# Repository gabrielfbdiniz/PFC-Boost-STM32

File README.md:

# AC-DC 380V Active Boost PFC Converter

-red.svg)

-purple.svg)

Conversor estático de potência CA/CC com **Correção Ativa do Fator de Potência (Active PFC)** na topologia **Boost**, projetado para elevar a tensão da rede elétrica retificada (127V / 220V AC) para um barramento CC estabilizado de **380V DC**.

O controle digital de malha fechada (tensão e corrente em modo de condução contínua - CCM) e gerenciamento de estados é operado por uma plataforma **STM32F103C8T6 (ARM Cortex-M3 a 72 MHz)**, acompanhado de proteções ultrarrápidas de sobrecorrente por hardware e circuito inteligente de pré-carga (*soft-start / inrush current limiting*).

---

## Renderizações 3D do Projeto

| Vista Superior (Top View) | Vista Inferior (Bottom View) |
| :---: | :---: |
|  |  |

| Perspectiva Superior Isométrica | Perspectiva Inferior Isométrica |
| :---: | :---: |
|  |  |

---

## 1. Visão Geral da Arquitetura do Conversor

O sistema é dividido em três blocos funcionais modulares conforme o esquemático hierárquico:
1. **Low Frequency Rectifier & Inrush (`lf_rectifier`):** Ponte retificadora de entrada, relé de bypass de inrush (`RELAY_INRUSH`) e relé mestre de ligamento (`RELAY_ON_OFF`).
2. **Estágio de Potência & Proteção PFC (`pfc`):** Indutor boost, MOSFET de comutação rápida, diodo boost ultrarrápido, gate driver com porta de intertravamento e latch analógico de sobrecorrente em hardware.
3. **Placa de Controle & IHM (`mcu`):** Breakout STM32F103 (Blue Pill), conversores de nível lógico, display I2C, encoder rotativo e acionamento térmico do ventilador.

```mermaid
flowchart LR
    subgraph AC_Input["Entrada de Rede"]
        AC["Rede CA (127V / 220V)"] --> INRUSH["Circuito de Pré-carga & Inrush"]
        INRUSH --> BRIDGE["Ponte Retificadora"]
    end

    subgraph PFC_Stage["Estágio Boost PFC (Alta Tensão)"]
        BRIDGE -->|"V_in retificada"| L["Indutor Boost L1"]
        L --> Q["MOSFET Q3"]
        L --> D["Diodo Boost D15"]
        D --> COUT["Banco Capacitivo (380V DC)"]
        Q --> SHUNT["Sensor de Corrente"]
    end

    subgraph Hardware_Protection["Proteção Hardware OCP"]
        SHUNT --> COMP["Comparador Rápido (LMV7219)"]
        COMP --> LATCH["Latch SR (74HC00)"]
        LATCH -->|"Hard-Trip Inibição"| AND_GATE["Porta AND (74LVC1G08)"]
        AND_GATE --> DRIVER["Gate Driver TC4427"]
        DRIVER --> Q
    end

    subgraph MCU_Control["Controle Digital (STM32 Blue Pill)"]
        COUT -.->|"Sensoriamento Vout (ADC)"| MCU["STM32F103C8T6"]
        BRIDGE -.->|"Sensoriamento Vin (ADC)"| MCU
        SHUNT -.->|"Sensoriamento IL (ADC)"| MCU
        MCU -->|"PWM Alta Frequência"| AND_GATE
        MCU -->|"RESET_OC"| LATCH
        MCU -->|"ENABLE Geral"| AND_GATE
        MCU -->|"Comando Relés"| INRUSH
    end
```

---

## 2. Especificações Técnicas

| Parâmetro | Valor / Faixa | Observações |
| :--- | :--- | :--- |
| **Topologia** | Boost PFC Ativo (CCM) | Fator de Potência $> 0.98$ |
| **Tensão de Entrada ($V_{in}$)** | $127\text{ V}_{\text{RMS}} - 220\text{ V}_{\text{RMS}}$ ($60\text{ Hz}$) | Tensão de pico retificada: $\approx 180\text{ V} - 311\text{ V}$ |
| **Tensão de Saída ($V_{out}$)** | **$380\text{ V DC}$ regulada** | Tensão nominal do barramento CC |
| **Controlador** | STM32F103C8T6 (ARM Cortex-M3) | 72 MHz, 64 KB Flash, ADC 12 bits |
| **Chaveamento Principal** | MOSFET TO-220 + Diodo Boost TO-220 | Dissipadores dimensionados para convecção forçada |
| **Driver de Gate** | Microchip TC4427 + Intertravamento 74LVC1G08 | Resposta sub-microssegundo |
| **Proteção de Sobrecorrente (OCP)** | Comparador LMV7219 + Latch 74HC00 | Desligamento por hardware independente do MCU |
| **Pré-carga de Barramento** | Relés de 2 estágios (`INRUSH` e `ON_OFF`) | Protege diodos e banco capacitivo na energização |
| **Interface do Usuário** | Display I2C + Encoder Rotativo com Push-Button | Navegação de menus, leituras e parametrização |
| **Refrigeração** | Saída controlada de 12V para Ventoinha | Acionamento via transistor comutada por PWM/GPIO |

---

## 3. Pinout & Mapeamento do Microcontrolador (STM32 Blue Pill)

O mapeamento de pinos reflete as conexões reais implementadas nas folhas esquemáticas em [`hardware/`](hardware/) e roteadas na placa de circuito impresso:

### Pinos de Potência, Controle e Atuadores

| Pino Blue Pill | Sinal Associado | Função no Hardware | Descrição / Operação |
| :--- | :--- | :--- | :--- |
| **`PA2`** | `PFC_PWM` | `TIM2_CH3` | Sinal PWM de alta frequência (50 a 100 kHz) para comutação do MOSFET via gate driver |
| **`PB10`** | `RELAY_INRUSH`| GPIO Output | Aciona o relé de limitação de corrente de partida (bypass do termistor NTC) |
| **`PB11`** | `RELAY_ON_OFF`| GPIO Output | Aciona o relé principal de energização da rede CA |
| **`PB12`** | `FAN_CTRL` | GPIO Output | Controle liga/desliga da ventoinha de refrigeração forçada |
| **`PB8`** | `I2C1_SCL` | `I2C1` | Clock do barramento serial I2C (Display OLED 0.96" SSD1306) com pull-up de 4.7kΩ |
| **`PB9`** | `I2C1_SDA` | `I2C1` | Dados do barramento serial I2C (Display OLED 0.96" SSD1306) com pull-up de 4.7kΩ |
| **`PB3`** | `EXP_SCK` | `SPI1_SCK` / GPIO | Barramento de expansão frontal / Interface de usuário (`J2`) |
| **`PB4`** | `EXP_MISO` | `SPI1_MISO` / GPIO | Barramento de expansão frontal / Interface de usuário (`J2`) |
| **`PB5`** | `EXP_MOSI` | `SPI1_MOSI` / GPIO | Barramento de expansão frontal / Interface de usuário (`J2`) |
| **`PA15`** | `EXP_CS` | GPIO Output | Chip-select para periféricos de expansão no conector `J2` |

### Sensoriamento Analógico e Medição

| Pino Blue Pill | Sinal Associado | Função no Hardware | Descrição / Operação |
| :--- | :--- | :--- | :--- |
| **`PA7`** | `PFC_IL` | `ADC1_IN7` | Sensoriamento analógico da corrente no indutor boost (amplificador de shunt) |
| **`PB0`** | `PFC_VOUT`| `ADC1_IN8` | Sensoriamento da tensão de saída do barramento CC estabilizado (380V) |
| **`PB1`** | `PFC_VIN` | `ADC1_IN9` | Sensoriamento da tensão senoidal retificada de entrada |
| **`PC13`** | *LED Onboard* | GPIO Output | LED indicador de batimento cardíaco (*heartbeat*) e status operacional |
| **`PA13`/`PA14`** | `SWD` | `SWDIO` / `SWCLK` | Interface de gravação e depuração em tempo real com ST-Link v2 |

## 4. Circuitos de Proteção e Segurança em Hardware

1. **Proteção Ultrarrápida de Sobrecorrente (Hardware Trip):**
   * Em conversores boost, sobrecorrentes na chave podem queimar semicondutores em microssegundos.
   * O sinal do resistor shunt de corrente é monitorado continuamente pelo comparador analógico **LMV7219** (`U2`).
   * A saída do comparador aciona imediatamente um **Latch SR implementado com portas NAND 74HC00** (`U5`), travando a saída em nível lógico baixo e cortando a porta AND `74LVC1G08` (`U6`) antes mesmo do firmware do MCU tomar conhecimento.
   * O destravamento após mitigação só ocorre mediante pulso explícito do pino `RESET_OC`.

2. **Sequenciamento de Energização e Pré-Carga:**
   * Na energização inicial, o relé `RELAY_INRUSH` comuta o fluxo de corrente por resistores limitadores de alta potência até os capacitores de saída carregarem sem picos destrutivos.
   * Ao atingir o patamar nominal de entrada, o relé mestre `RELAY_ON_OFF` fecha o circuito em paralelo e o conversor pode ser habilitado com segurança.

---

## 5. Estrutura do Repositório

```text
├── hardware/                   # Projeto de Hardware no KiCad 10
│   ├── 3d/                     # Modelos CAD 3D dos componentes (STEP / WRL)
│   │   ├── Capacitor_THT_L28.0mm_W11.0mm_P25.00mm.step # Modelo 3D dos capacitores C11 e C12
│   │   ├── Inductor_NEE-30-15-15.step                  # Modelo 3D do indutor boost L1 (NEE-30)
│   │   └── ...                 # Modelos adicionais (STM32 Blue Pill, bornes, conectores)
│   ├── lf_rectifier.kicad_sch  # Sub-folha: Retificação de baixa frequência e inrush
│   ├── mcu.kicad_sch           # Sub-folha: Módulo MCU Blue Pill e conexões de IHM
│   ├── pfc.kicad_sch           # Sub-folha: Estágio Boost PFC de 380V e circuitos de proteção
│   ├── power-supply.kicad_pcb  # Layout e roteamento completo da PCB
│   ├── power-supply.kicad_pro  # Arquivo de gerenciamento do projeto KiCad 10
│   └── power-supply.kicad_sch  # Esquemático principal (Top-Level Sheet)
├── firmware/                   # Firmware embarcado para STM32F103 (STM32CubeIDE 1.19)
│   └── README.md               # Guia de configuração, pinout, FSM e arquitetura
├── simulation/                 # Simulação computacional e controle
│   └── simulate_pfc_control.py # Comparação de malhas de controle (Cascata Energia vs. Jacobiano)
├── docs/                       # Documentação técnica e esquemáticos vetoriais
│   ├── PFC_380V_Schematic.pdf  # Esquemático completo exportado em PDF vetorial
│   └── pfc_control_comparison.png # Gráficos comparativos de controle
├── renders/                    # Renders 3D fotorrealistas em alta resolução (1080p)
│   ├── render_top.png
│   ├── render_bottom.png
│   ├── render_iso_top.png
│   └── render_iso_bottom.png
├── .gitignore                  # Filtro para temporários, builds e caches
├── LICENSE                     # Licença de Hardware Aberto CERN-OHL-S v2
└── README.md                   # Documentação técnica de engenharia
```

---

## 6. Como Abrir e Validar o Projeto

### Pré-requisitos
* **KiCad EDA 10.0+** instalado no sistema.
* **Python 3.10+** (com `numpy` e `matplotlib`) para as simulações numéricas.
* **STM32CubeIDE 1.19** para o desenvolvimento do firmware.

### Regenerar Renderizações 3D (via Linha de Comando)
```bash
kicad-cli pcb render -o renders/render_top.png --width 1920 --height 1080 --side top --quality high hardware/power-supply.kicad_pcb
kicad-cli pcb render -o renders/render_bottom.png --width 1920 --height 1080 --side bottom --quality high hardware/power-supply.kicad_pcb
kicad-cli pcb render -o renders/render_iso_top.png --width 1920 --height 1080 --rotate -45,0,45 --quality high hardware/power-supply.kicad_pcb
kicad-cli pcb render -o renders/render_iso_bottom.png --width 1920 --height 1080 --side bottom --rotate -45,0,45 --quality high hardware/power-supply.kicad_pcb
```

### Exportar Esquemático em PDF
```bash
kicad-cli sch export pdf -o docs/PFC_380V_Schematic.pdf hardware/power-supply.kicad_sch
```

### Executar a Simulação Comparativa de Controle
```bash
python simulation/simulate_pfc_control.py
```

## 7. Licença & Créditos

### Autores & Desenvolvedores
* **Abílio Davi**
* **Gabriel Diniz**
* **Vinicius Moreira**

### Orientação
* **Professor Colombo**
* **Professor Eduardo Lenz**

---

### Licença
Distribuído sob a licença **CERN-OHL-S v2** (*CERN Open Hardware Licence Strongly Reciprocal*). Consulte o arquivo [LICENSE](LICENSE) para mais detalhes.

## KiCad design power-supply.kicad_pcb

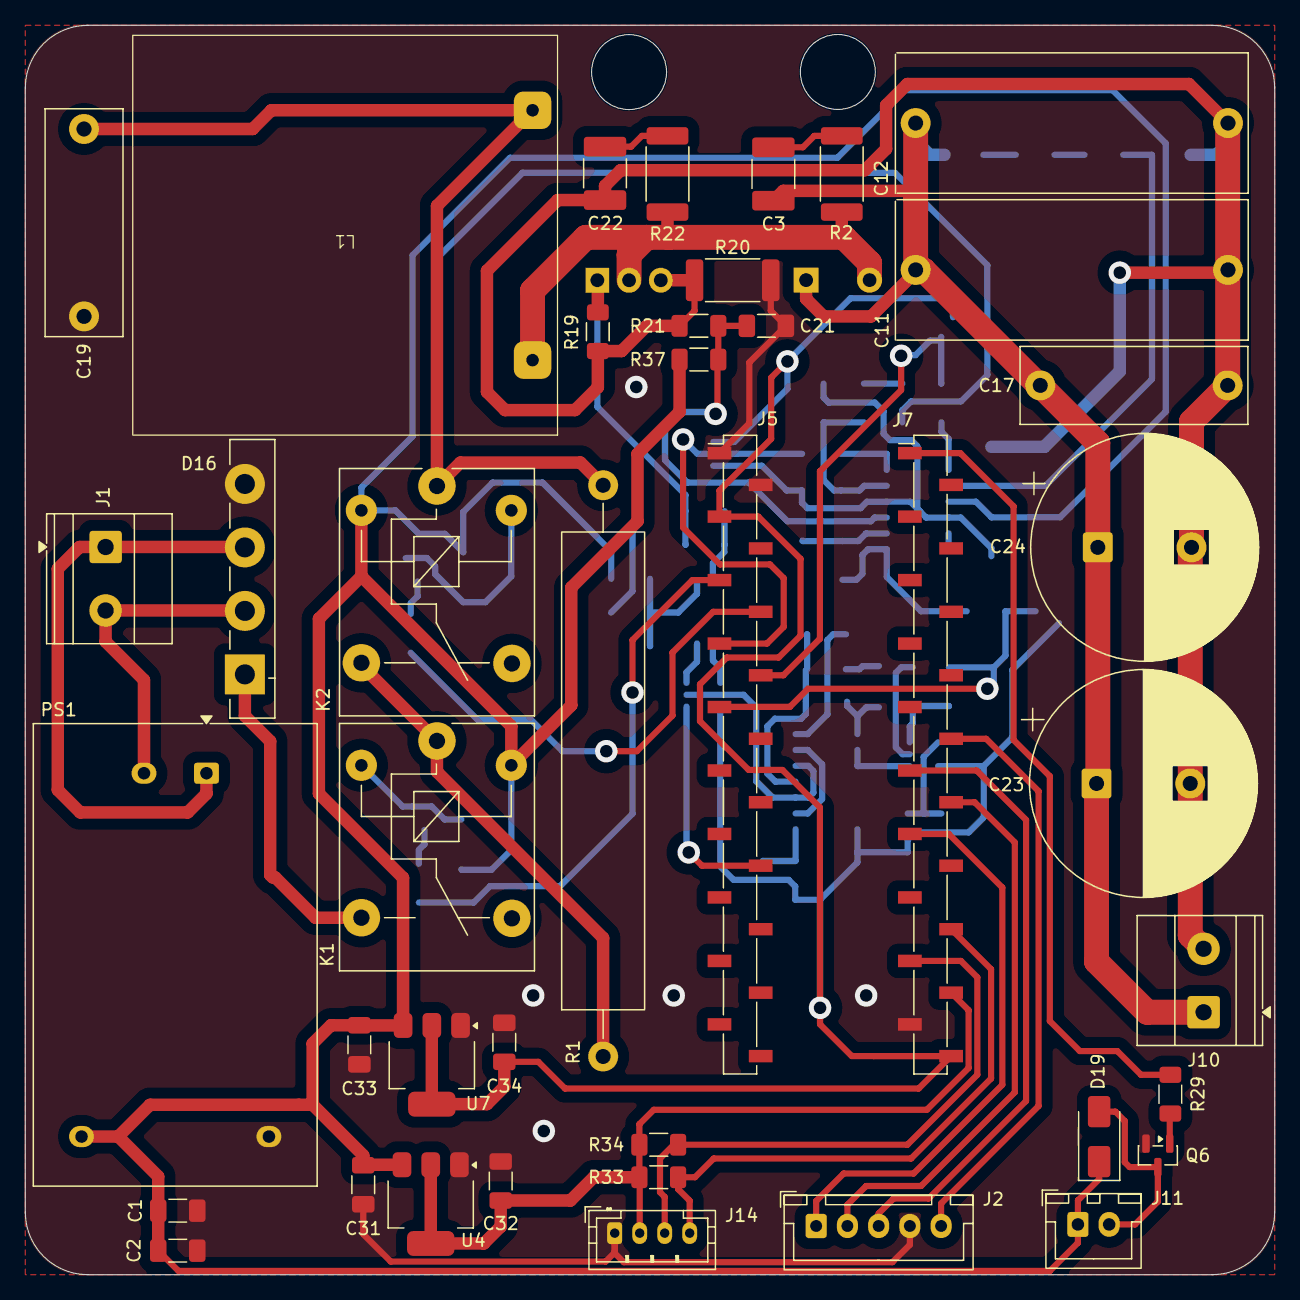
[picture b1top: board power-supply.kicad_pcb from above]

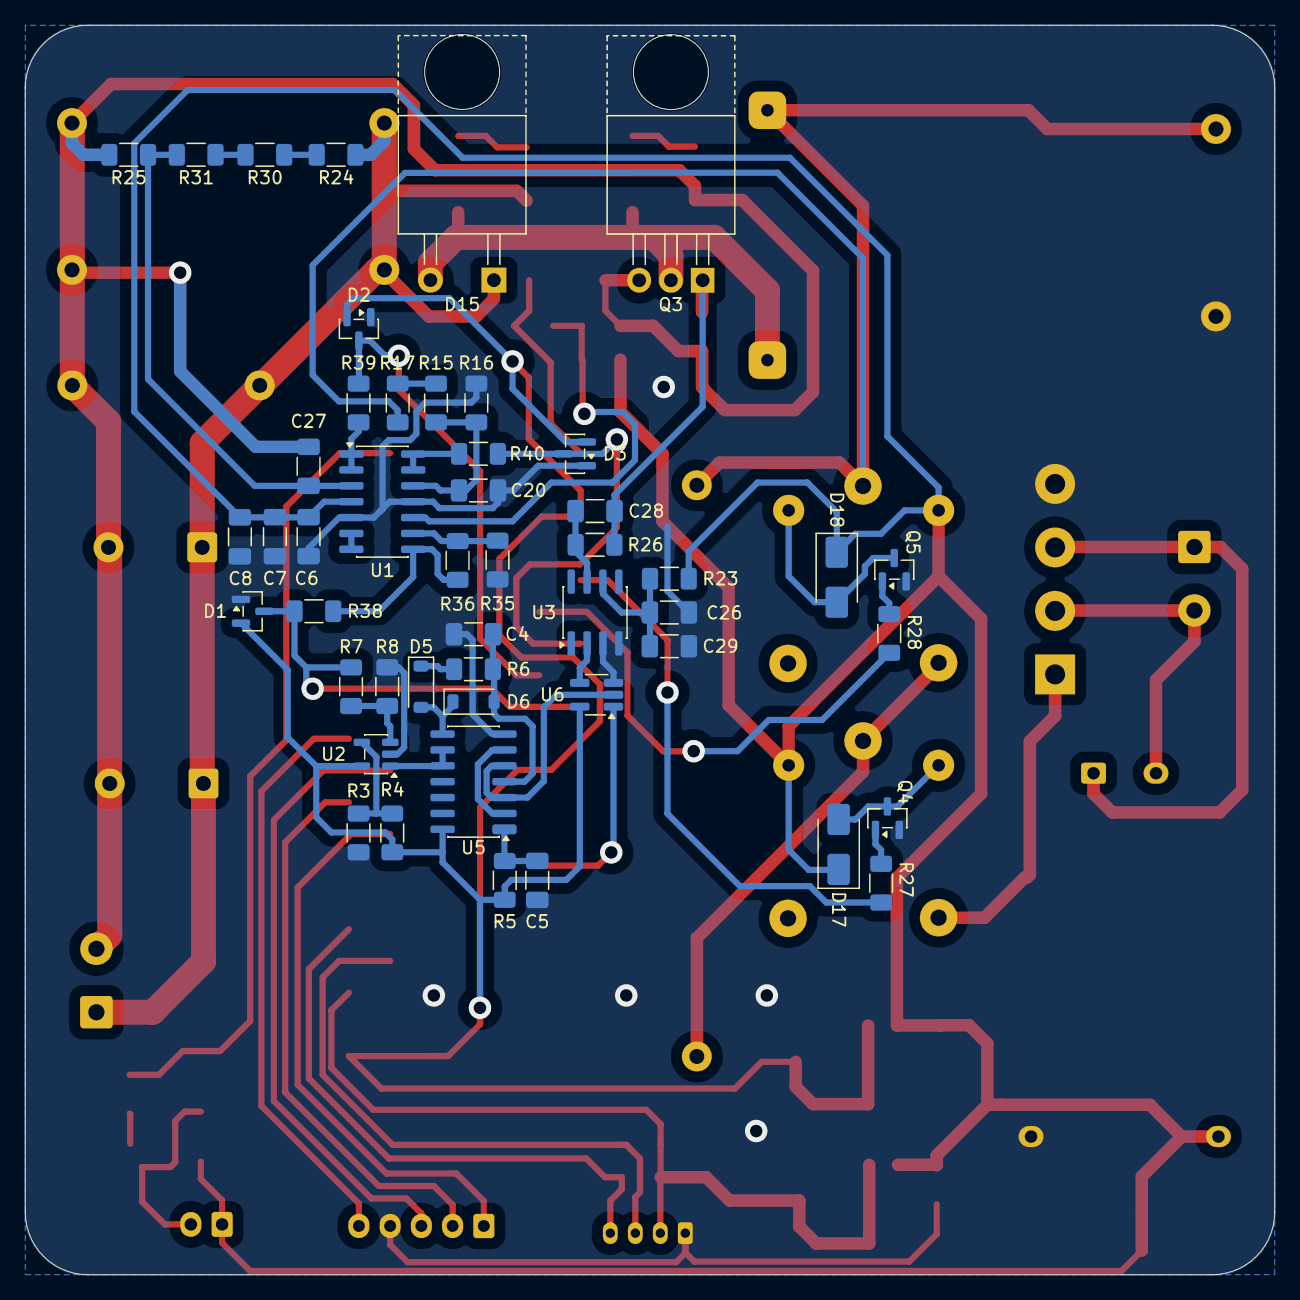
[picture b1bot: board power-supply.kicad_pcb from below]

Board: 2 copper layers, 100.0 x 100.0 mm, 89 parts (48 on the bottom side), 57 nets.

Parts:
C1, C2: 1u; C_1206_3216Metric_Pad1.33x1.80mm_HandSolder
C3: C; C_1812_4532Metric_Pad1.57x3.40mm_HandSolder
C4, C5, C6, C7, C8, C28, C29: 100nF; C_1206_3216Metric_Pad1.33x1.80mm_HandSolder
C11, C12: 1u/630V; Capacitorzao
C17, C19: 100nF/630V; C_Rect_L18.0mm_W6.0mm_P15.00mm_FKS3_FKP3
C20, C21, C27: XXXX; C_1206_3216Metric_Pad1.33x1.80mm_HandSolder
C22: XXXX/1000V; C_1812_4532Metric_Pad1.57x3.40mm_HandSolder
C23, C24: 100u/450V; CP_Radial_D18.0mm_P7.50mm
C26: 1uF; C_1206_3216Metric_Pad1.33x1.80mm_HandSolder
C31, C32, C33, C34: 10uF; C_1206_3216Metric_Pad1.33x1.80mm_HandSolder
D1, D2, D3: BAT54S; SOT-23
D5, D6: 1N4148W; D_SOD-123
D15: MUR1560; TO-220-2_Horizontal_TabUp
D16: GBU8J; Diode_Bridge_Vishay_GBU
D17, D18, D19: SS14; D_SMA
J1, J10: KRE; TerminalBlock_Phoenix_MKDS-1,5-2-5.08_1x02_P5.08mm_Horizont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
J2: Conn_01x05; JST_XH_B5B-XH-A_1x05_P2.50mm_Vertical
J5, J7: Conn_01x20; PinSocket_1x20_P2.54mm_Vertical_SMD_Pin1Left
J11: Fan; JST_XH_B2B-XH-A_1x02_P2.50mm_Vertical
J14: I2C; JST_PH_B4B-PH-K_1x04_P2.00mm_Vertical
K1, K2: Rele 5V; Relay_SPDT_SANYOU_SRD_Series_Form_C
L1: 2.2 mH; NEE-30-15-15
PS1: HLK-PM12; Converter_ACDC_Hi-Link_HLK-PMxx
Q3: IRF740; TO-220-3_Horizontal_TabUp
Q4, Q5, Q6: MMBT3904; SOT-23
R1: 330R; R_Axial_Power_L38.0mm_W6.4mm_P45.72mm
R2: R; R_2512_6332Metric_Pad1.40x3.35mm_HandSolder
R3: 20k; R_1206_3216Metric_Pad1.30x1.75mm_HandSolder
R4: 30k; R_1206_3216Metric_Pad1.30x1.75mm_HandSolder
R5, R7, R8: 10k; R_1206_3216Metric_Pad1.30x1.75mm_HandSolder
R6: 100k; R_1206_3216Metric_Pad1.30x1.75mm_HandSolder
R15, R17: 91k; R_1206_3216Metric_Pad1.30x1.75mm_HandSolder
R16, R25: 1k5; R_1206_3216Metric_Pad1.30x1.75mm_HandSolder
R19: 12k; R_1206_3216Metric_Pad1.30x1.75mm_HandSolder
R20: 0R1; R_2512_6332Metric_Pad1.40x3.35mm_HandSolder
R21, R27, R28, R29: 1k; R_1206_3216Metric_Pad1.30x1.75mm_HandSolder
R22: XXXX; R_2512_6332Metric_Pad1.40x3.35mm_HandSolder
R23: 47R; R_1206_3216Metric_Pad1.30x1.75mm_HandSolder
R24, R30: 56k; R_1206_3216Metric_Pad1.30x1.75mm_HandSolder
R26: 10R; R_1206_3216Metric_Pad1.30x1.75mm_HandSolder
R31: 68k; R_1206_3216Metric_Pad1.30x1.75mm_HandSolder
R33, R34: 4k7; R_1206_3216Metric_Pad1.30x1.75mm_HandSolder
R35: 22k; R_1206_3216Metric_Pad1.30x1.75mm_HandSolder
R36: 150k; R_1206_3216Metric_Pad1.30x1.75mm_HandSolder
R37: R_1206_3216Metric_Pad1.30x1.75mm_HandSolder
R38, R39, R40: 390R; R_1206_3216Metric_Pad1.30x1.75mm_HandSolder
U1: LM324; SOIC-14_3.9x8.7mm_P1.27mm
U2: LMV7219M5; SOT-23-5
U3: TC4427; SOIC-8_3.9x4.9mm_P1.27mm
U4: AMS1117-5.0; SOT-223-3_TabPin2
U5: 74HC00; SOIC-14_3.9x8.7mm_P1.27mm
U6: 74LVC1G08; SOT-23-5_HandSoldering
U7: AMS1117-3.3; SOT-223-3_TabPin2

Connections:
+3V3: C34.1, D1.2 (K), D2.2 (K), D3.2 (K), J5.3, J7.20, R4.1, R5.1, U2.5 (V+), U5.14 (VCC), U6.5 (VCC), U7.2 (VO)
+5V: C32.1, J7.18, J14.2, R33.1, R34.1, U4.2 (VO)
+12V: C1.1, C2.1, C6.1, C7.1, C8.1, C31.1, C33.1, D17.1 (K), D18.1 (K), D19.1 (K), J11.1, K1.5, K2.2, PS1.4 (+Vout), R23.2, R37.1, U1.4 (V+), U4.3 (VI), U7.3 (VI)
/L: D16.3, J1.1, PS1.1 (AC/L)
/Low Frequency Rectifier/DC_311V: C19.2, K2.1, L1.2, R1.2, R17.1
/MCU/PA2: J5.14, U6.1
/MCU/PA7: D1.3 (COM), J5.9, R7.1, R38.2
/MCU/PA15: J2.5, J7.10
/MCU/PB0: D2.3 (COM), J5.8, R39.2
/MCU/PB1: D3.3 (COM), J5.7, R40.2
/MCU/PB3: J2.3, J7.11
/MCU/PB4: J2.2, J7.12
/MCU/PB5: J2.1, J7.13
/MCU/PB8: J7.16, J14.4, R33.2
/MCU/PB9: J7.17, J14.3, R34.2
/MCU/PB10: J5.6, R28.2
/MCU/PB11: J5.5, R27.2
/MCU/PB12: J7.1, R29.1
/N: D16.2, J1.2, PS1.2 (AC/N)
/PFC/DC_380V: C3.2, C11.2, C12.2, C17.2, C23.1, C24.1, D15.1 (K), J10.1, R24.1
/PFC/ENABLE: U5.3, U5.5, U6.2
/PFC/GATE_BOOST: C28.2, Q3.1 (G), R19.1, R26.2
/PFC/GND_380V: C11.1, C12.1, C17.1, C22.2, C23.2, C24.2, C27.2, J10.2, Q3.3 (S), R19.2, R20.1, R21.1, R25.2
/PFC/INDUCTOR_OUT: D15.2 (A), L1.1, Q3.2 (D), R2.1, R22.2
/PFC/RESET_OC: C5.1, R5.2, U5.1
/PFC/VIN_RAW: C20.1, R15.2, R16.1, U1.12 (+)
/PFC/VOUT_RAW: C27.1, R25.1, R31.2, U1.3 (+)
GND_311V: C1.2, C2.2, C4.2, C5.2, C6.2, C7.2, C8.2, C19.1, C20.2, C21.2, C26.2, C29.2, C31.2, C32.2, C33.2, C34.2, D1.1 (A), D2.1 (A), D3.1 (A), D16.4 (-), J2.4, J5.1, J5.2, J7.19, J14.1, PS1.3 (-Vout), Q4.2 (E), Q5.2 (E), Q6.2 (E), R3.2, R8.2, R16.2, R20.2, R35.2, U1.5 (+), U1.11 (V-), U2.2 (V-), U3.3 (GND), U3.4 (IN_B), U4.1 (GND), U5.7 (GND), U6.3 (GND), U7.1 (GND)
unnamed: C3.1, R2.2
unnamed: C22.1, R22.1
unnamed: D5.2 (A), D6.1 (K), U5.8
unnamed: D5.1 (K), R6.1
unnamed: C4.1, D6.2 (A), R6.2, U5.4
unnamed: D16.1 (+), K1.3
unnamed: D17.2 (A), K1.2, Q4.3 (C)
unnamed: D18.2 (A), K2.5, Q5.3 (C)
unnamed: D19.2 (A), J11.2, Q6.3 (C)
unnamed: K1.1, K2.3, R1.1
unnamed: Q4.1 (B), R27.1
unnamed: Q5.1 (B), R28.1
unnamed: Q6.1 (B), R29.2
unnamed: R15.1, R17.2
unnamed: R24.2, R30.1
unnamed: R30.2, R31.1
unnamed: R36.2, R38.1, U1.8
unnamed: R39.1, U1.1, U1.2 (-)
unnamed: U1.6 (-), U1.7
unnamed: C21.1, R21.2, R37.2, U1.10 (+)
unnamed: R35.1, R36.1, U1.9 (-)
unnamed: R40.1, U1.13 (-), U1.14
unnamed: R7.2, R8.1, U2.3 (+)
unnamed: R3.1, R4.2, U2.4 (-)
unnamed: U2.1, U5.9, U5.10
unnamed: U3.2 (IN_A), U6.4
unnamed: C28.1, R26.1, U3.7 (OUT_A)
unnamed: C26.1, C29.1, R23.1, U3.6 (V+)
unnamed: U5.2, U5.6

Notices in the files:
README.md:
License: CERN-OHL-S v2
